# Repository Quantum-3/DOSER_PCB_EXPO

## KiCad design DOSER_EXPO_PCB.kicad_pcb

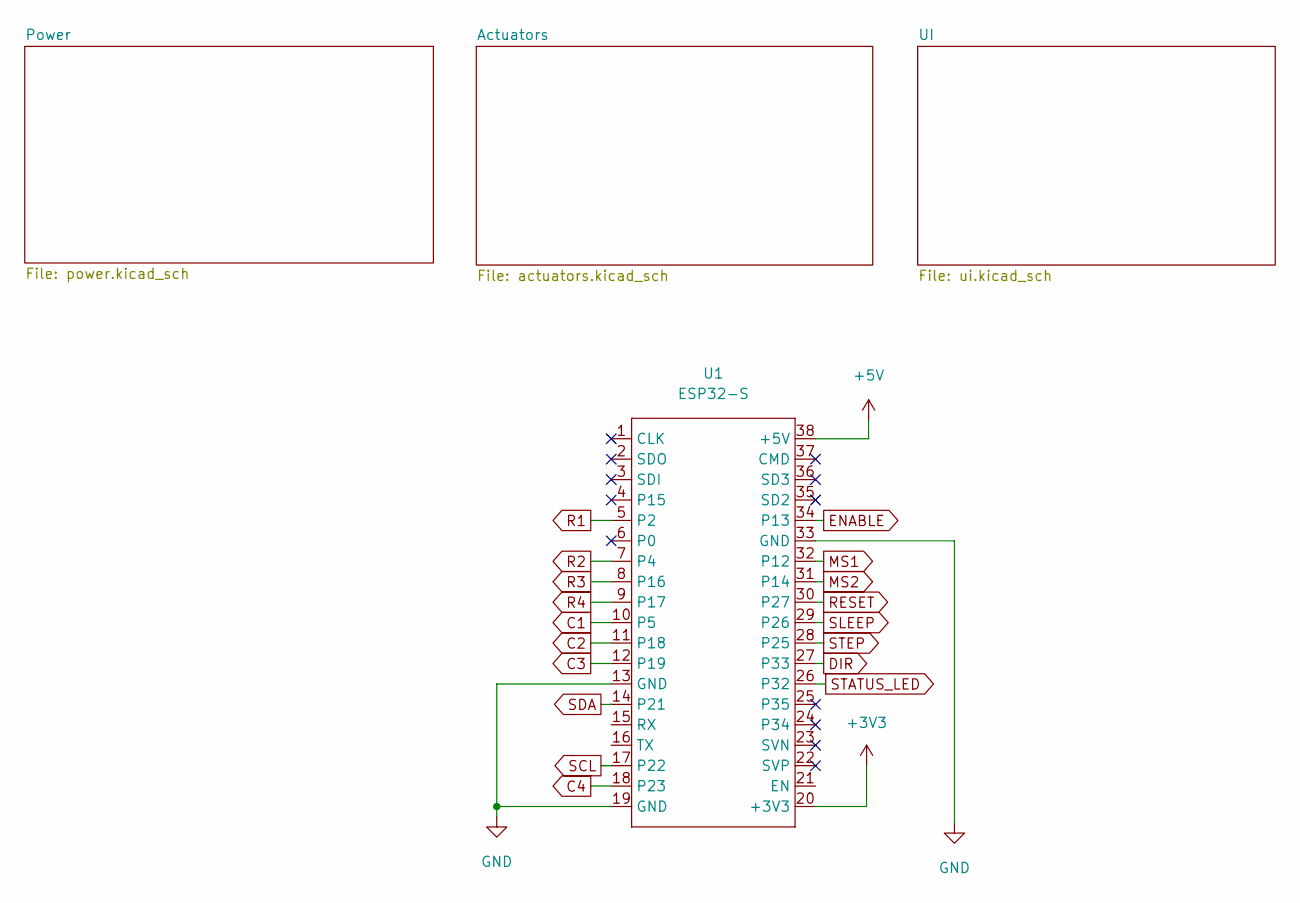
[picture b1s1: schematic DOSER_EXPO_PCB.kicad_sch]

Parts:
U1: ESP32-S

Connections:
+3V3: U1.20 (+3V3); also elsewhere on the board
+5V: U1.38 (+5V); also elsewhere on the board
C1: U1.10 (P5); also elsewhere on the board
C2: U1.11 (P18); also elsewhere on the board
C3: U1.12 (P19); also elsewhere on the board
C4: U1.18 (P23); also elsewhere on the board
DIR: U1.27 (P33); also elsewhere on the board
ENABLE: U1.34 (P13); also elsewhere on the board
GND: U1.13 (GND), U1.19 (GND), U1.33 (GND); also elsewhere on the board
MS1: U1.32 (P12); also elsewhere on the board
MS2: U1.31 (P14); also elsewhere on the board
R1: U1.5 (P2); also elsewhere on the board
R2: U1.7 (P4); also elsewhere on the board
R3: U1.8 (P16); also elsewhere on the board
R4: U1.9 (P17); also elsewhere on the board
RESET: U1.30 (P27); also elsewhere on the board
SCL: U1.17 (P22); also elsewhere on the board
SDA: U1.14 (P21); also elsewhere on the board
SLEEP: U1.29 (P26); also elsewhere on the board
STATUS_LED: U1.26 (P32); also elsewhere on the board
STEP: U1.28 (P25); also elsewhere on the board

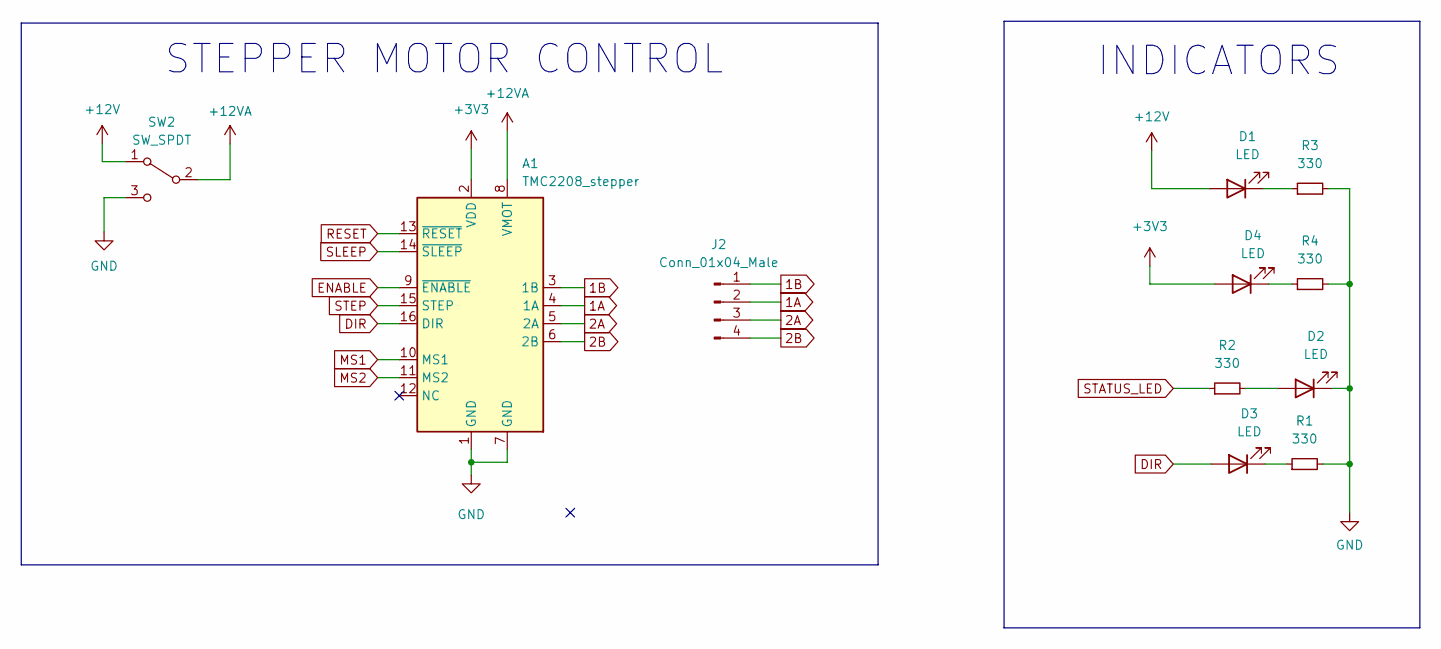
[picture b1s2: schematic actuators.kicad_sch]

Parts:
A1: TMC2208_stepper; Stepper driver
D1, D2, D3, D4: LED; PinHeader_1x02_P2.54mm_Vertical
J2: Conn_01x04_Male; JST_XH_B4B-XH-A_1x04_P2.50mm_Vertical
R1, R2, R3, R4: 330; R_Axial_DIN0207_L6.3mm_D2.5mm_P10.16mm_Horizontal
SW2: SW_SPDT; KCD1-1 switch

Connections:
1A: A1.4 (1A), J2.2
1B: A1.3 (1B), J2.1
2A: A1.5 (2A), J2.3
2B: A1.6 (2B), J2.4
+3V3: A1.2 (VDD), D4.2 (A); also elsewhere on the board
+12V: D1.2 (A), SW2.1 (A); also elsewhere on the board
+12VA: A1.8 (VMOT), SW2.2 (B)
DIR: A1.16 (DIR), D3.2 (A); also elsewhere on the board
ENABLE: A1.9 (~ENABLE); also elsewhere on the board
GND: A1.1 (GND), A1.7 (GND), D2.1 (K), R1.2, R3.2, R4.2, SW2.3 (C); also elsewhere on the board
MS1: A1.10 (MS1); also elsewhere on the board
MS2: A1.11 (MS2); also elsewhere on the board
unnamed: D1.1 (K), R3.1
unnamed: D3.1 (K), R1.1
unnamed: D4.1 (K), R4.1
unnamed: D2.2 (A), R2.2
RESET: A1.13 (~RESET); also elsewhere on the board
SLEEP: A1.14 (~SLEEP); also elsewhere on the board
STATUS_LED: R2.1; also elsewhere on the board
STEP: A1.15 (STEP); also elsewhere on the board

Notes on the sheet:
STEPPER MOTOR CONTROL
INDICATORS

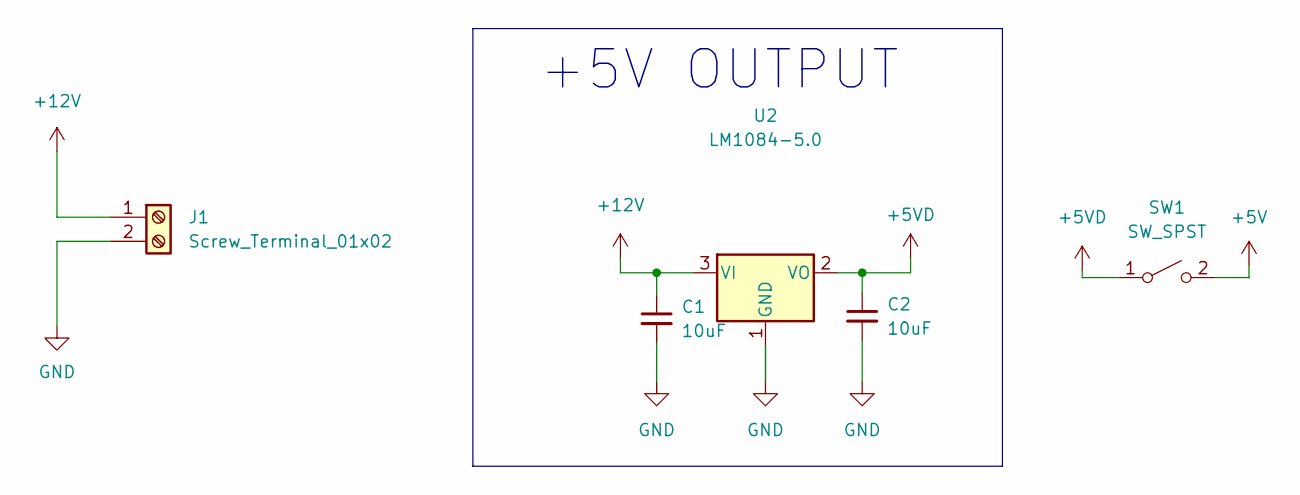
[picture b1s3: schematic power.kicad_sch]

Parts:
C1, C2: 10uF; CP_Radial_D5.0mm_P2.50mm
J1: Screw_Terminal_01x02; TerminalBlock_Phoenix_MKDS-1,5-2-5.08_1x02_P5.08mm_Horizont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
SW1: SW_SPST; KCD1 switch
U2: LM1084-5.0; TO-220-3_Vertical

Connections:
+5V: SW1.2 (B); also elsewhere on the board
+5VD: C2.1, SW1.1 (A), U2.2 (VO)
+12V: C1.1, J1.1, U2.3 (VI); also elsewhere on the board
GND: C1.2, C2.2, J1.2, U2.1 (GND); also elsewhere on the board

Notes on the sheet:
+5V OUTPUT

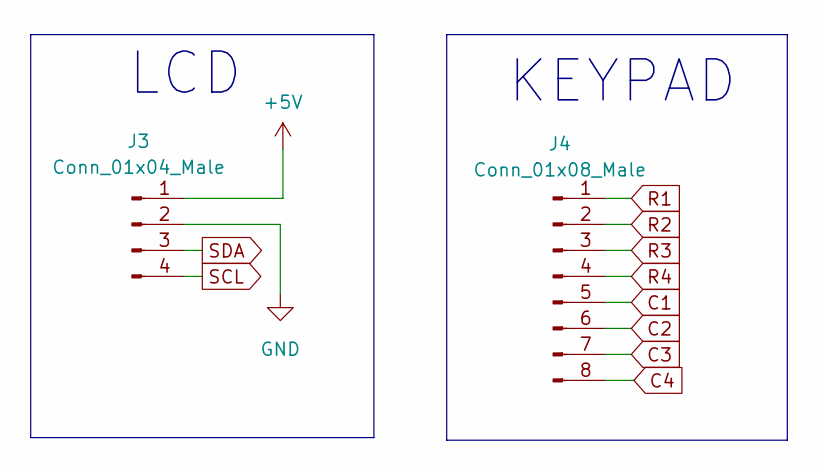
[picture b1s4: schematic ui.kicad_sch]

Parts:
J3: Conn_01x04_Male; PinHeader_1x04_P2.54mm_Vertical
J4: Conn_01x08_Male; PinHeader_1x08_P2.54mm_Vertical

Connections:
+5V: J3.1; also elsewhere on the board
C1: J4.5; also elsewhere on the board
C2: J4.6; also elsewhere on the board
C3: J4.7; also elsewhere on the board
C4: J4.8; also elsewhere on the board
GND: J3.2; also elsewhere on the board
R1: J4.1; also elsewhere on the board
R2: J4.2; also elsewhere on the board
R3: J4.3; also elsewhere on the board
R4: J4.4; also elsewhere on the board
SCL: J3.4; also elsewhere on the board
SDA: J3.3; also elsewhere on the board

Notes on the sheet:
LCD
KEYPAD

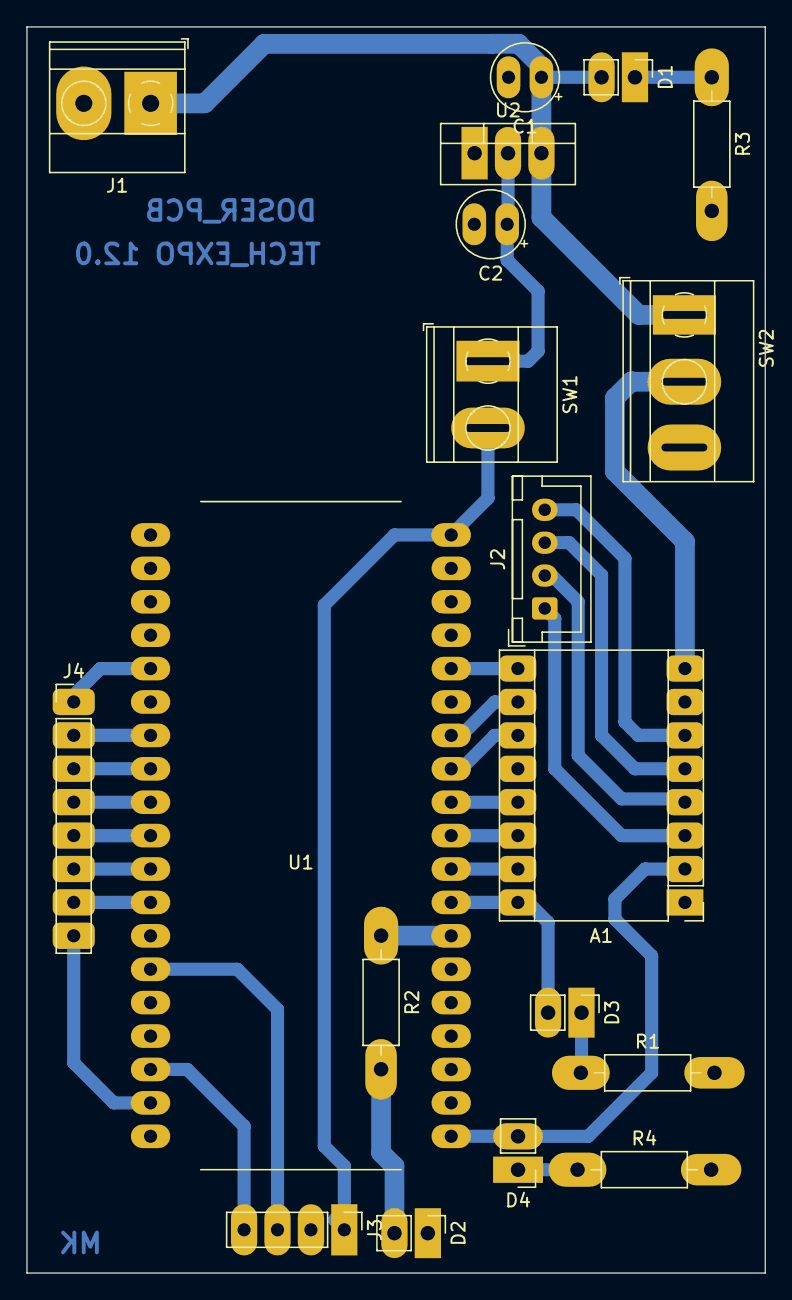
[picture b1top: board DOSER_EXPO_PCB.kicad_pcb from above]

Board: 2 copper layers, 56.1 x 94.7 mm, 19 parts (0 on the bottom side), 32 nets.

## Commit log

2022-11-17 Ready for tech expo
